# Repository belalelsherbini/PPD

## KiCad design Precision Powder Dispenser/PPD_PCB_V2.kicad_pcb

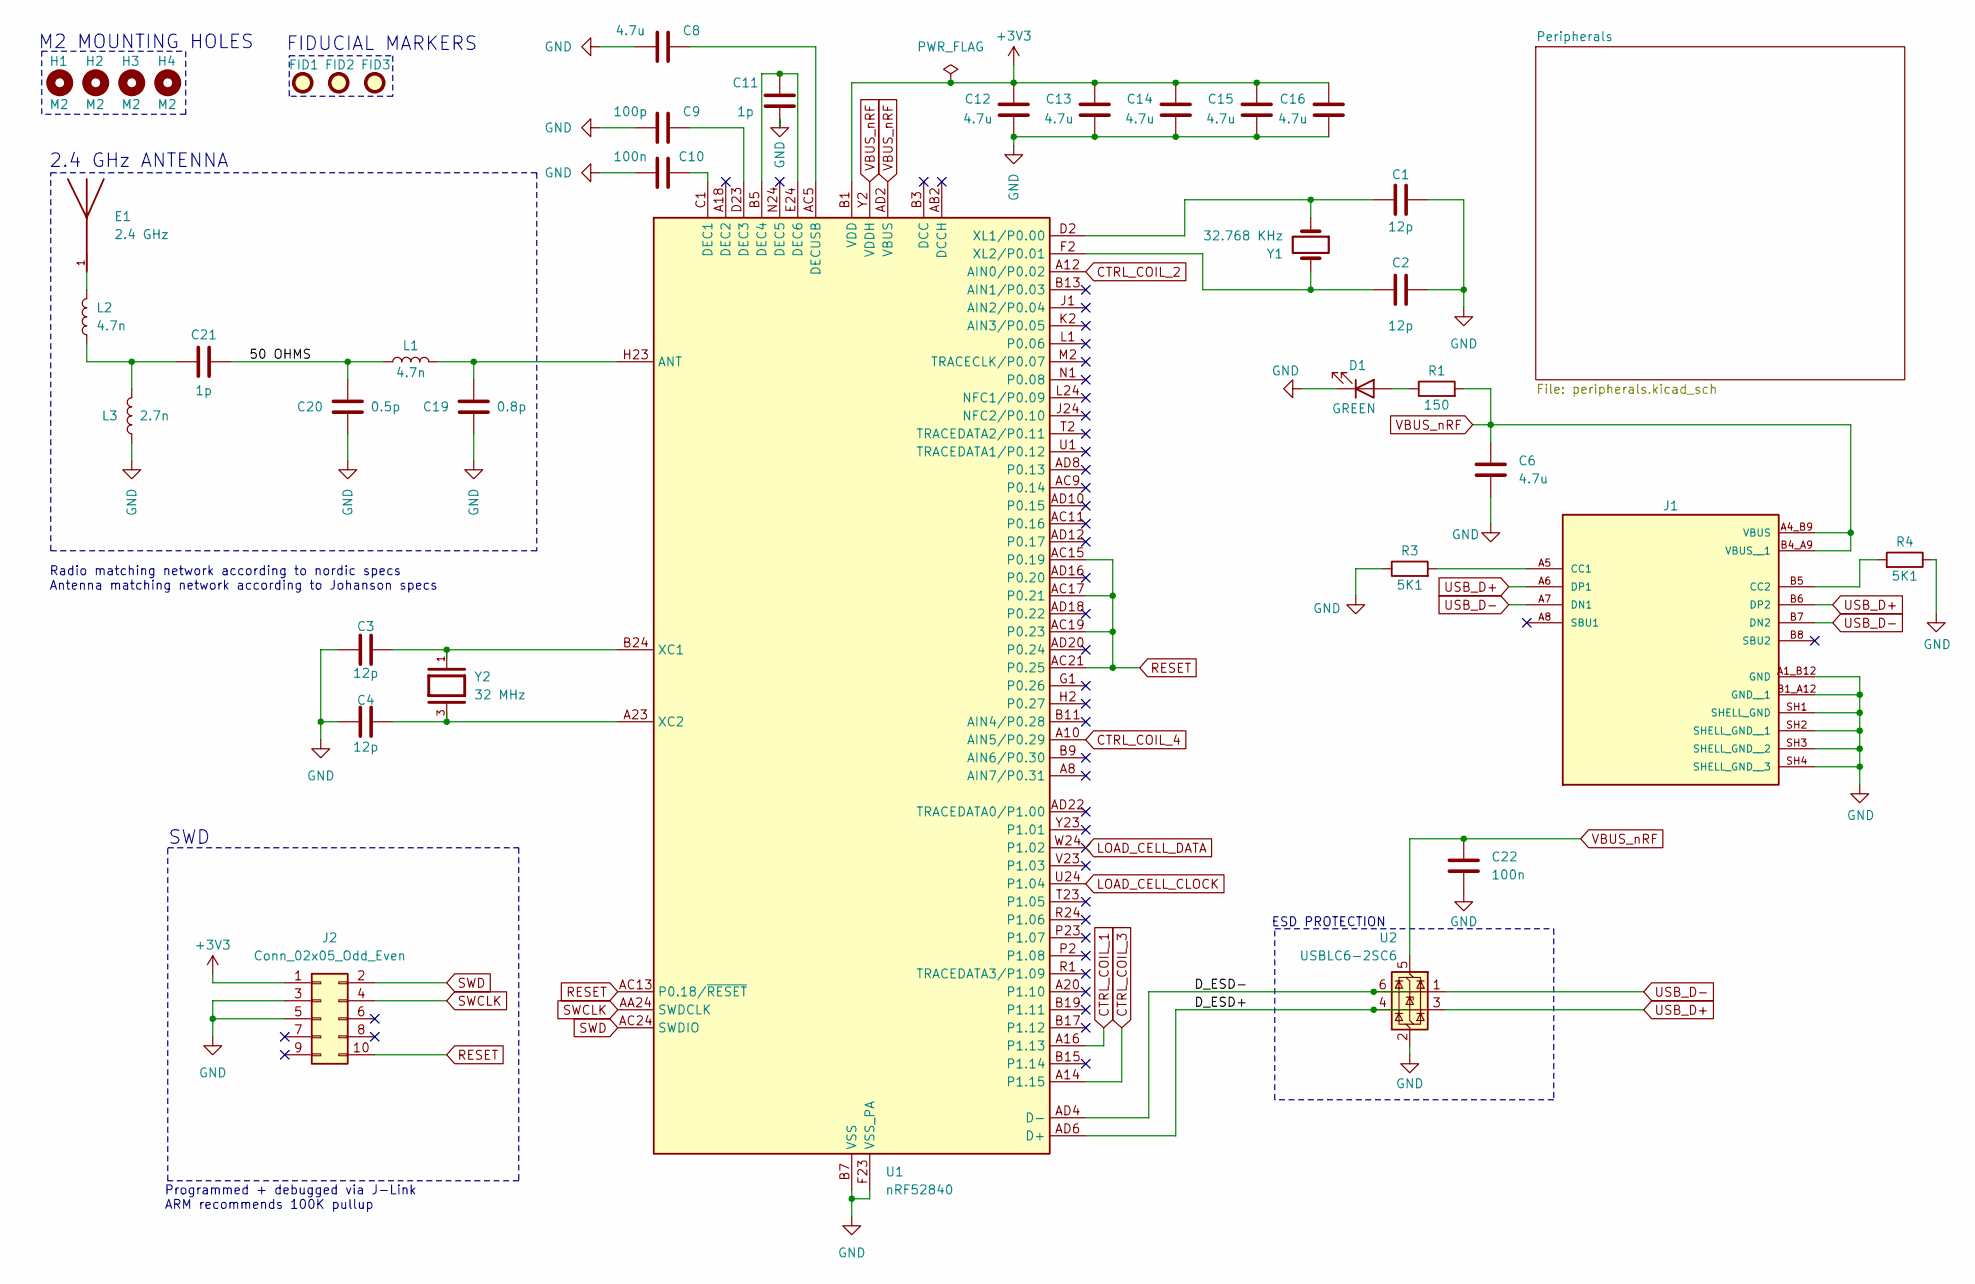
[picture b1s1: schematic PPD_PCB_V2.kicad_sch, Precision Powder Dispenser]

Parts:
C1, C2, C3, C4: 12p; C_0402_1005Metric
C6, C8, C12, C13, C14, C15, C16: 4.7u; C_0402_1005Metric
C9: 100p; C_0402_1005Metric
C10, C22: 100n; C_0402_1005Metric
C11, C21: 1p; C_0402_1005Metric
C19: 0.8p; C_0402_1005Metric
C20: 0.5p; C_0402_1005Metric
D1: GREEN; LED_0603_1608Metric
E1: 2.4 GHz; 2450AT18A100E_JOT; PARTREV 4.0
FID1, FID2, FID3: Fiducial; Fiducial_0.5mm_Mask1mm
H1, H2, H3, H4: M2; MountingHole_2.2mm_M2
J1: USB4105-GF-A; GCT_USB4105-GF-A; PARTREV B4
J2: Conn_02x05_Odd_Even; AMPHENOL_20021521-00010C1LF
L1, L2: 4.7n; L_0402_1005Metric
L3: 2.7n; L_0402_1005Metric
R1: 150; R_0603_1608Metric
R3, R4: 5K1; R_0603_1608Metric
U1: nRF52840; Nordic_AQFN-73-1EP_7x7mm_P0.5mm
U2: USBLC6-2SC6; SOT-23-6
Y1: 32.768 KHz; XTAL_ECS-.327-9-34B-TR
Y2: 32 MHz; OSC_XRCGB32M000F2P01R0; PARTREV N/A

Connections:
+3V3: C12.2, C13.2, C14.2, C15.2, C16.2, J2.1, U1.A22 (VDD), U1.AD14 (VDD), U1.AD23 (VDD), U1.B1 (VDD), U1.W1 (VDD); also elsewhere on the board
/50 OHMS: C20.2, C21.2, L1.1
/D_ESD+: U1.AD6 (D+), U2.4 (I/O2)
/D_ESD-: U1.AD4 (D-), U2.6 (I/O1)
CTRL_COIL_1: U1.A16 (P1.13); also elsewhere on the board
CTRL_COIL_2: U1.A12 (AIN0/P0.02); also elsewhere on the board
CTRL_COIL_3: U1.A14 (P1.15); also elsewhere on the board
CTRL_COIL_4: U1.A10 (AIN5/P0.29); also elsewhere on the board
GND: C1.2, C2.2, C3.1, C4.1, C6.2, C8.1, C9.1, C10.1, C11.1, C12.1, C13.1, C14.1, C15.1, C16.1, C19.1, C20.1, C22.2, D1.1 (K), J1.A1_B12 (GND), J1.B1_A12 (GND__1), J1.SH1 (SHELL_GND), J1.SH2 (SHELL_GND__1), J1.SH3 (SHELL_GND__2), J1.SH4 (SHELL_GND__3), J2.3, J2.5, L3.1, R3.1, R4.1, U1.B7 (VSS), U1.EP (VSS), U1.F23 (VSS_PA), U2.2 (GND); also elsewhere on the board
LOAD_CELL_CLOCK: U1.U24 (P1.04); also elsewhere on the board
LOAD_CELL_DATA: U1.W24 (P1.02); also elsewhere on the board
unnamed: C21.1, L2.1, L3.2
unnamed: D1.2 (A), R1.1
unnamed: E1.1, L2.2
unnamed: J1.A5 (CC1), R3.2
unnamed: J1.B5 (CC2), R4.2
unnamed: C19.2, L1.2, U1.H23 (ANT)
unnamed: C10.2, U1.C1 (DEC1)
unnamed: C9.2, U1.D23 (DEC3)
unnamed: C11.2, U1.B5 (DEC4), U1.E24 (DEC6)
unnamed: C8.2, U1.AC5 (DECUSB)
unnamed: C3.2, U1.B24 (XC1), Y2.1
unnamed: C4.2, U1.A23 (XC2), Y2.3
unnamed: C1.1, U1.D2 (XL1/P0.00), Y1.1
unnamed: C2.1, U1.F2 (XL2/P0.01), Y1.2
RESET: J2.10, U1.AC13 (P0.18/~RESET), U1.AC15 (P0.19), U1.AC17 (P0.21), U1.AC19 (P0.23), U1.AC21 (P0.25)
SWCLK: J2.4, U1.AA24 (SWDCLK)
SWD: J2.2, U1.AC24 (SWDIO)
USB_D+: J1.A6 (DP1), J1.B6 (DP2), U2.3 (I/O2)
USB_D-: J1.A7 (DN1), J1.B7 (DN2), U2.1 (I/O1)
VBUS_nRF: C6.1, C22.1, J1.A4_B9 (VBUS), J1.B4_A9 (VBUS__1), R1.2, U1.AD2 (VBUS), U1.Y2 (VDDH), U2.5 (VBUS)

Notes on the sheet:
SWD
2.4 GHz ANTENNA
ESD PROTECTION
Programmed + debugged via J-Link ARM recommends 100K pullup
M2 MOUNTING HOLES
FIDUCIAL MARKERS
Radio matching network according to nordic specs Antenna matching network according to Johanson specs

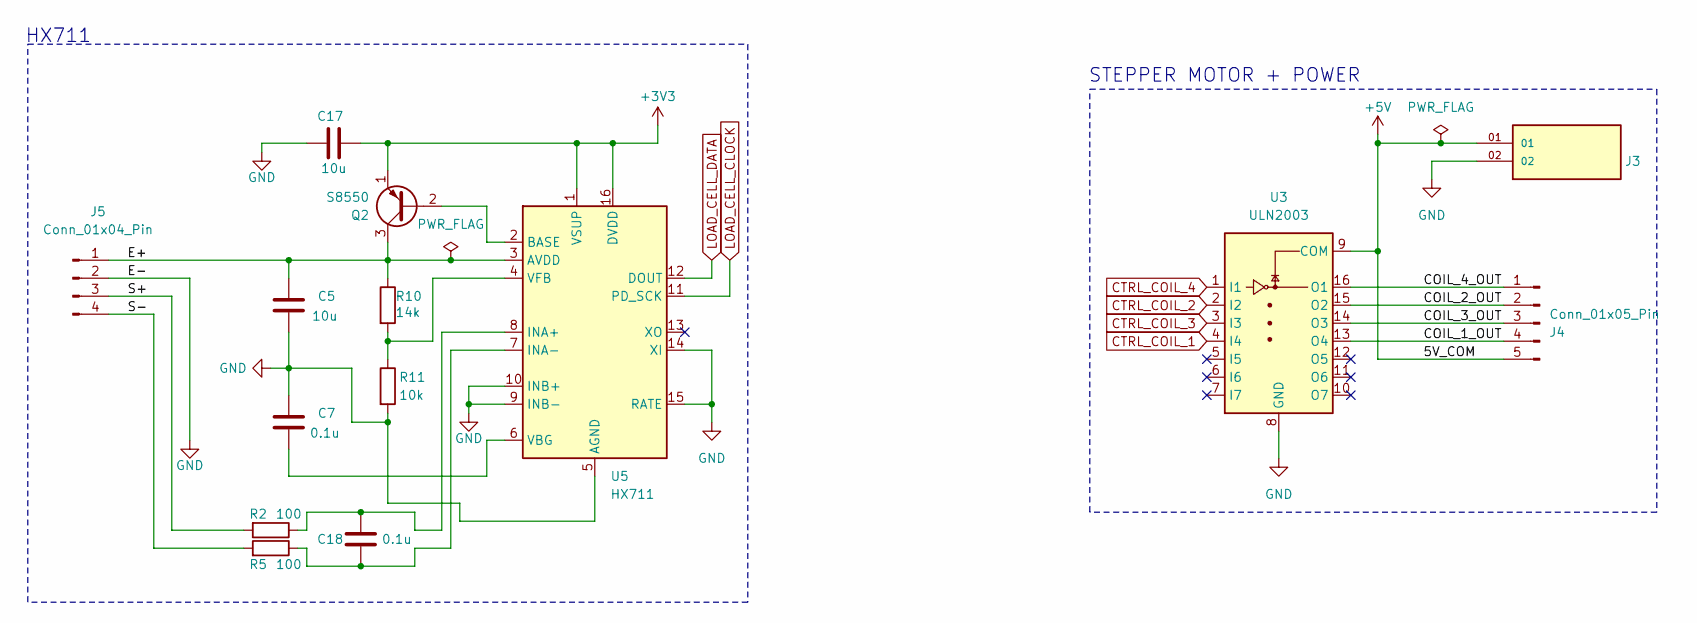
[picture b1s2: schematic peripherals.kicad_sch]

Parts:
C5, C17: 10u; C_0603_1608Metric
C7, C18: 0.1u; C_0402_1005Metric
J3: TS-102-T-A; SAMTEC_TS-102-T-A; PARTREV R
J4: Conn_01x05_Pin; JST_B5B-XH-A
J5: Conn_01x04_Pin; 250104
Q2: S8550; SOT-23_MCC-L
R2, R5: 100; R_0603_1608Metric
R10: 14k; R_0603_1608Metric
R11: 10k; R_0603_1608Metric
U3: ULN2003; SO-16_STM-M
U5: HX711; SOP-16_3.9x9.9mm_P1.27mm

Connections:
+3V3: C17.2, Q2.1 (E), U5.1 (VSUP), U5.16 (DVDD); also elsewhere on the board
+5V: J3.01, J4.5, U3.9 (COM)
/Peripherals/COIL_1_OUT: J4.4, U3.13 (O4)
/Peripherals/COIL_2_OUT: J4.2, U3.15 (O2)
/Peripherals/COIL_3_OUT: J4.3, U3.14 (O3)
/Peripherals/COIL_4_OUT: J4.1, U3.16 (O1)
/Peripherals/E+: C5.1, J5.1, Q2.3 (C), R10.1, U5.3 (AVDD)
/Peripherals/S+: J5.3, R2.2
/Peripherals/S-: J5.4, R5.2
CTRL_COIL_1: U3.4 (I4); also elsewhere on the board
CTRL_COIL_2: U3.2 (I2); also elsewhere on the board
CTRL_COIL_3: U3.3 (I3); also elsewhere on the board
CTRL_COIL_4: U3.1 (I1); also elsewhere on the board
GND: C5.2, C7.1, C17.1, J3.02, J5.2, R11.2, U3.8 (GND), U5.5 (AGND), U5.9 (INB-), U5.10 (INB+), U5.14 (XI), U5.15 (RATE); also elsewhere on the board
LOAD_CELL_CLOCK: U5.11 (PD_SCK); also elsewhere on the board
LOAD_CELL_DATA: U5.12 (DOUT); also elsewhere on the board
unnamed: Q2.2 (B), U5.2 (BASE)
unnamed: C18.1, R2.1, U5.8 (INA+)
unnamed: C18.2, R5.1, U5.7 (INA-)
unnamed: C7.2, U5.6 (VBG)
unnamed: R10.2, R11.1, U5.4 (VFB)

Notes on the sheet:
HX711
STEPPER MOTOR + POWER

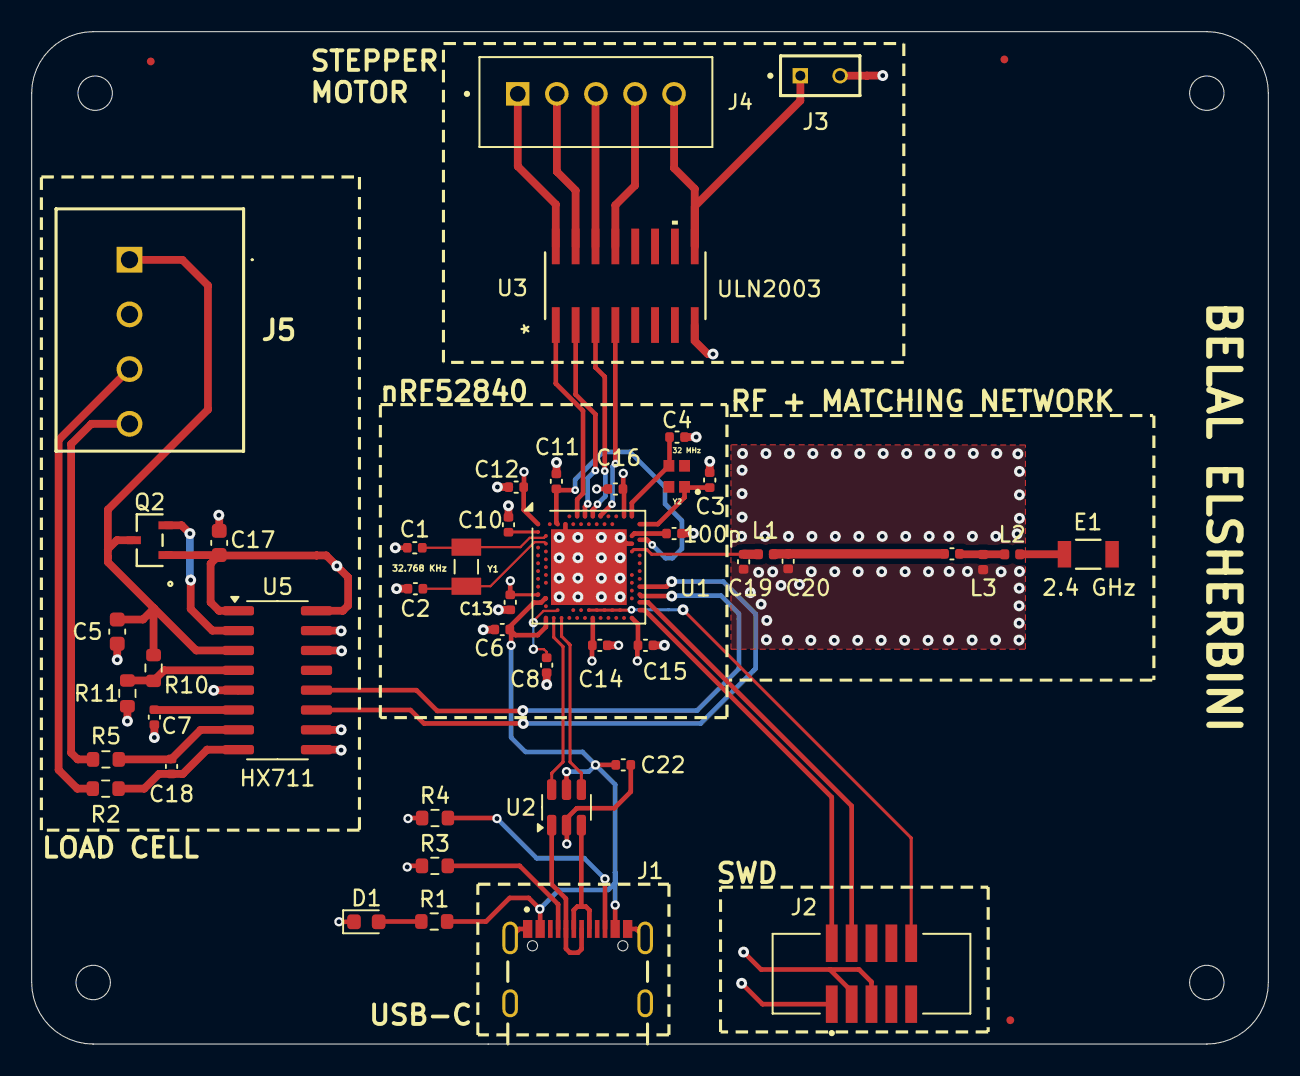
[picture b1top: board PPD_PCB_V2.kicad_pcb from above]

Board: 4 copper layers, 79.1 x 64.8 mm, 53 parts (0 on the bottom side), 44 nets.
